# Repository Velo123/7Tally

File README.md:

# 7Tally

DRC config imported from: https://github.com/Cimos/KiCad-CustomDesignRules/tree/main#

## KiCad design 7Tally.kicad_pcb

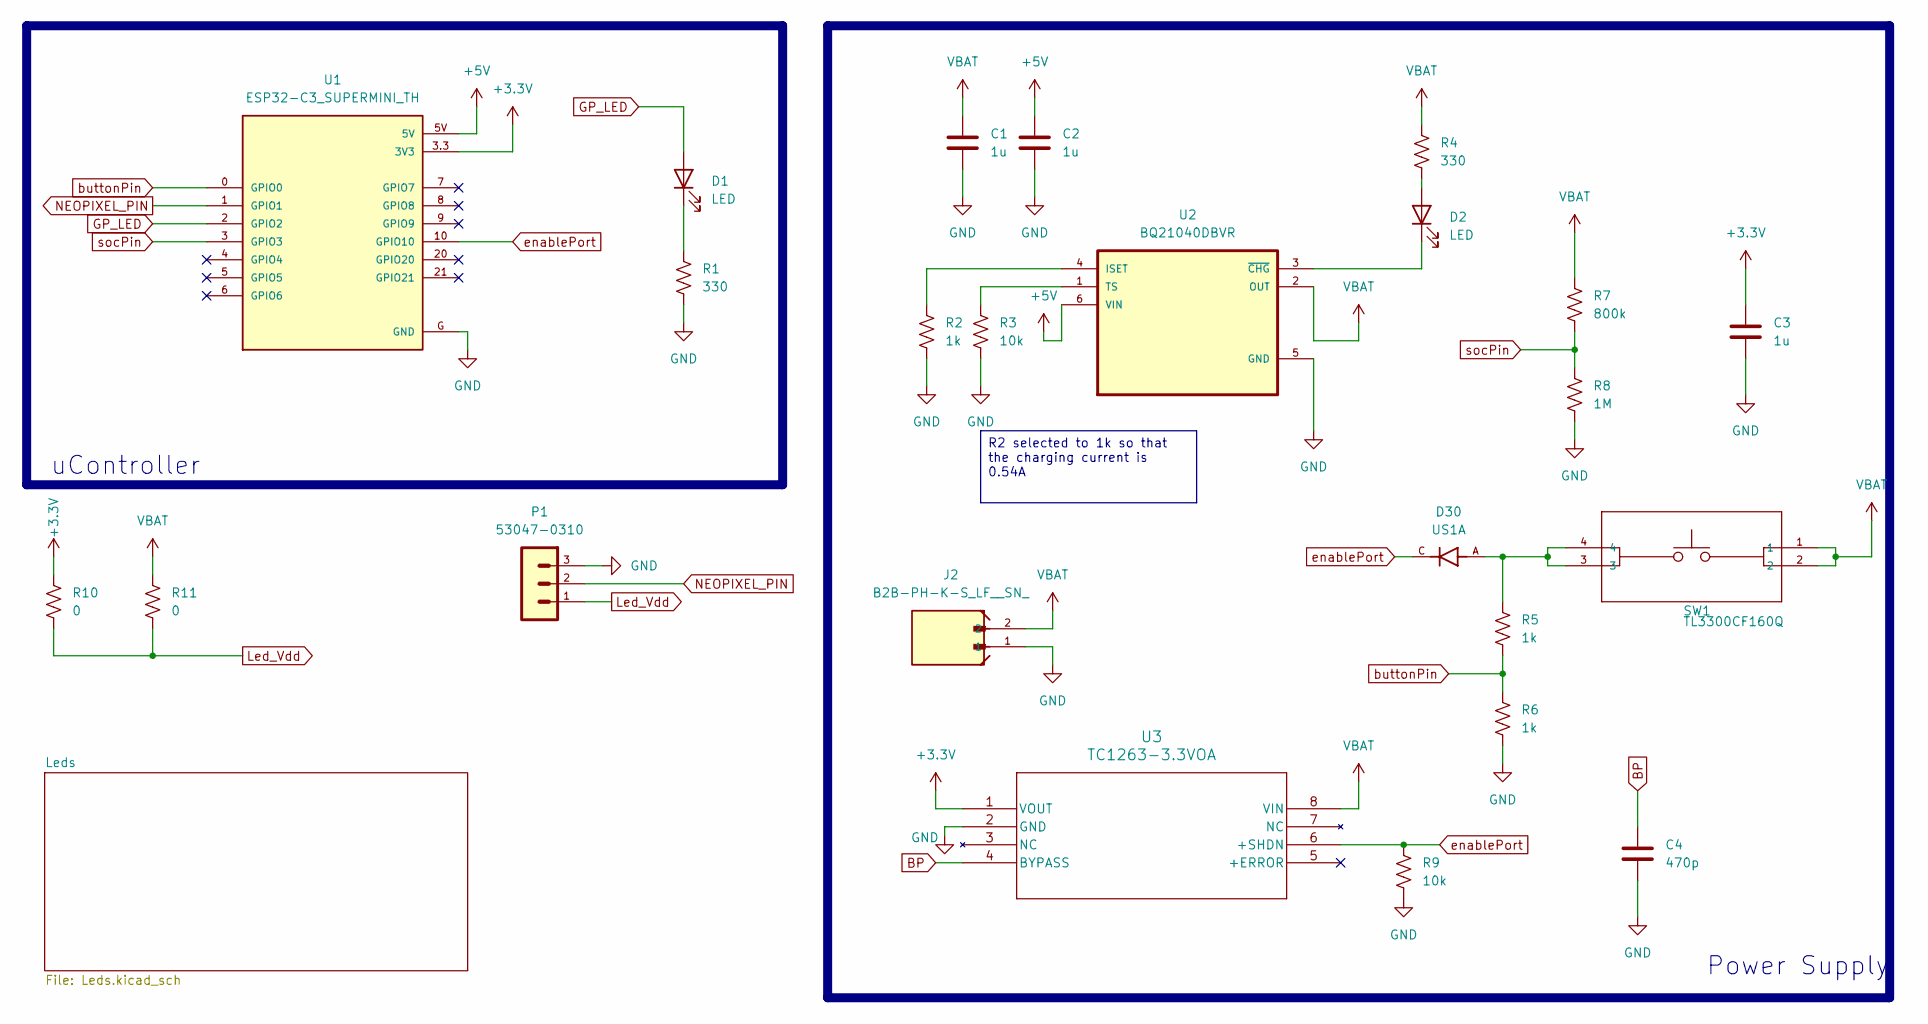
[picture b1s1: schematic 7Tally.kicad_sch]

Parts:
C1, C2, C3: 1u; C_0805_2012Metric
C4: 470p; C_0805_2012Metric
D1, D2: LED; LED_0805_2012Metric
D30: US1A; DIOM4325X250N; PARTREV L2102
J2: B2B-PH-K-S_LF__SN_; JST_B2B-PH-K-S_LF__SN_
P1: 53047-0310
R1, R4: 330; R_0805_2012Metric
R2, R5, R6: 1k; R_0805_2012Metric
R3, R9: 10k; R_0805_2012Metric
R7: 800k; R_0805_2012Metric
R8: 1M; R_0805_2012Metric
R10, R11: 0; R_0805_2012Metric
SW1: TL3300CF160Q; SW_TL3300CF160Q_EWI; MANUFACTURER_PART_NUMBER TL3300CF160Q
U1: ESP32-C3_SUPERMINI_TH; MODULE_ESP32-C3_SUPERMINI_TH
U2: BQ21040DBVR; SOT95P280X145-6N
U3: TC1263-3.3VOA; TC1263-3-3VOA_SOIC8-N_MC_MCH

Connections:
+3.3V: C3.1, R10.1, U1.3.3 (3V3), U3.1 (VOUT)
+5V: C2.1, U1.5V, U2.6 (VIN)
BP: C4.1, U3.4 (BYPASS)
GND: C1.2, C2.2, C3.2, C4.2, J2.1, P1.3, R1.2, R2.2, R3.2, R6.2, R8.2, R9.2, U1.G (GND), U2.5 (GND), U3.2 (GND); also elsewhere on the board
GP_LED: D1.2 (A), U1.2 (GPIO2)
Led_Vdd: P1.1, R10.2, R11.2; also elsewhere on the board
NEOPIXEL_PIN: P1.2, U1.1 (GPIO1); also elsewhere on the board
unnamed: D1.1 (K), R1.1
unnamed: D2.2 (A), R4.2
unnamed: D2.1 (K), U2.3 (~CHG)
unnamed: D30.A, R5.1, SW1.3, SW1.4
unnamed: R2.1, U2.4 (ISET)
unnamed: R3.1, U2.1 (TS)
VBAT: C1.1, J2.2, R4.1, R7.1, R11.1, SW1.1, SW1.2, U2.2 (OUT), U3.8 (VIN)
buttonPin: R5.2, R6.1, U1.0 (GPIO0)
enablePort: D30.C, R9.1, U1.10 (GPIO10), U3.6 (+SHDN)
socPin: R7.2, R8.1, U1.3 (GPIO3)

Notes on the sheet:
uController
Power Supply
R2 selected to 1k so that the charging current is 0.54A

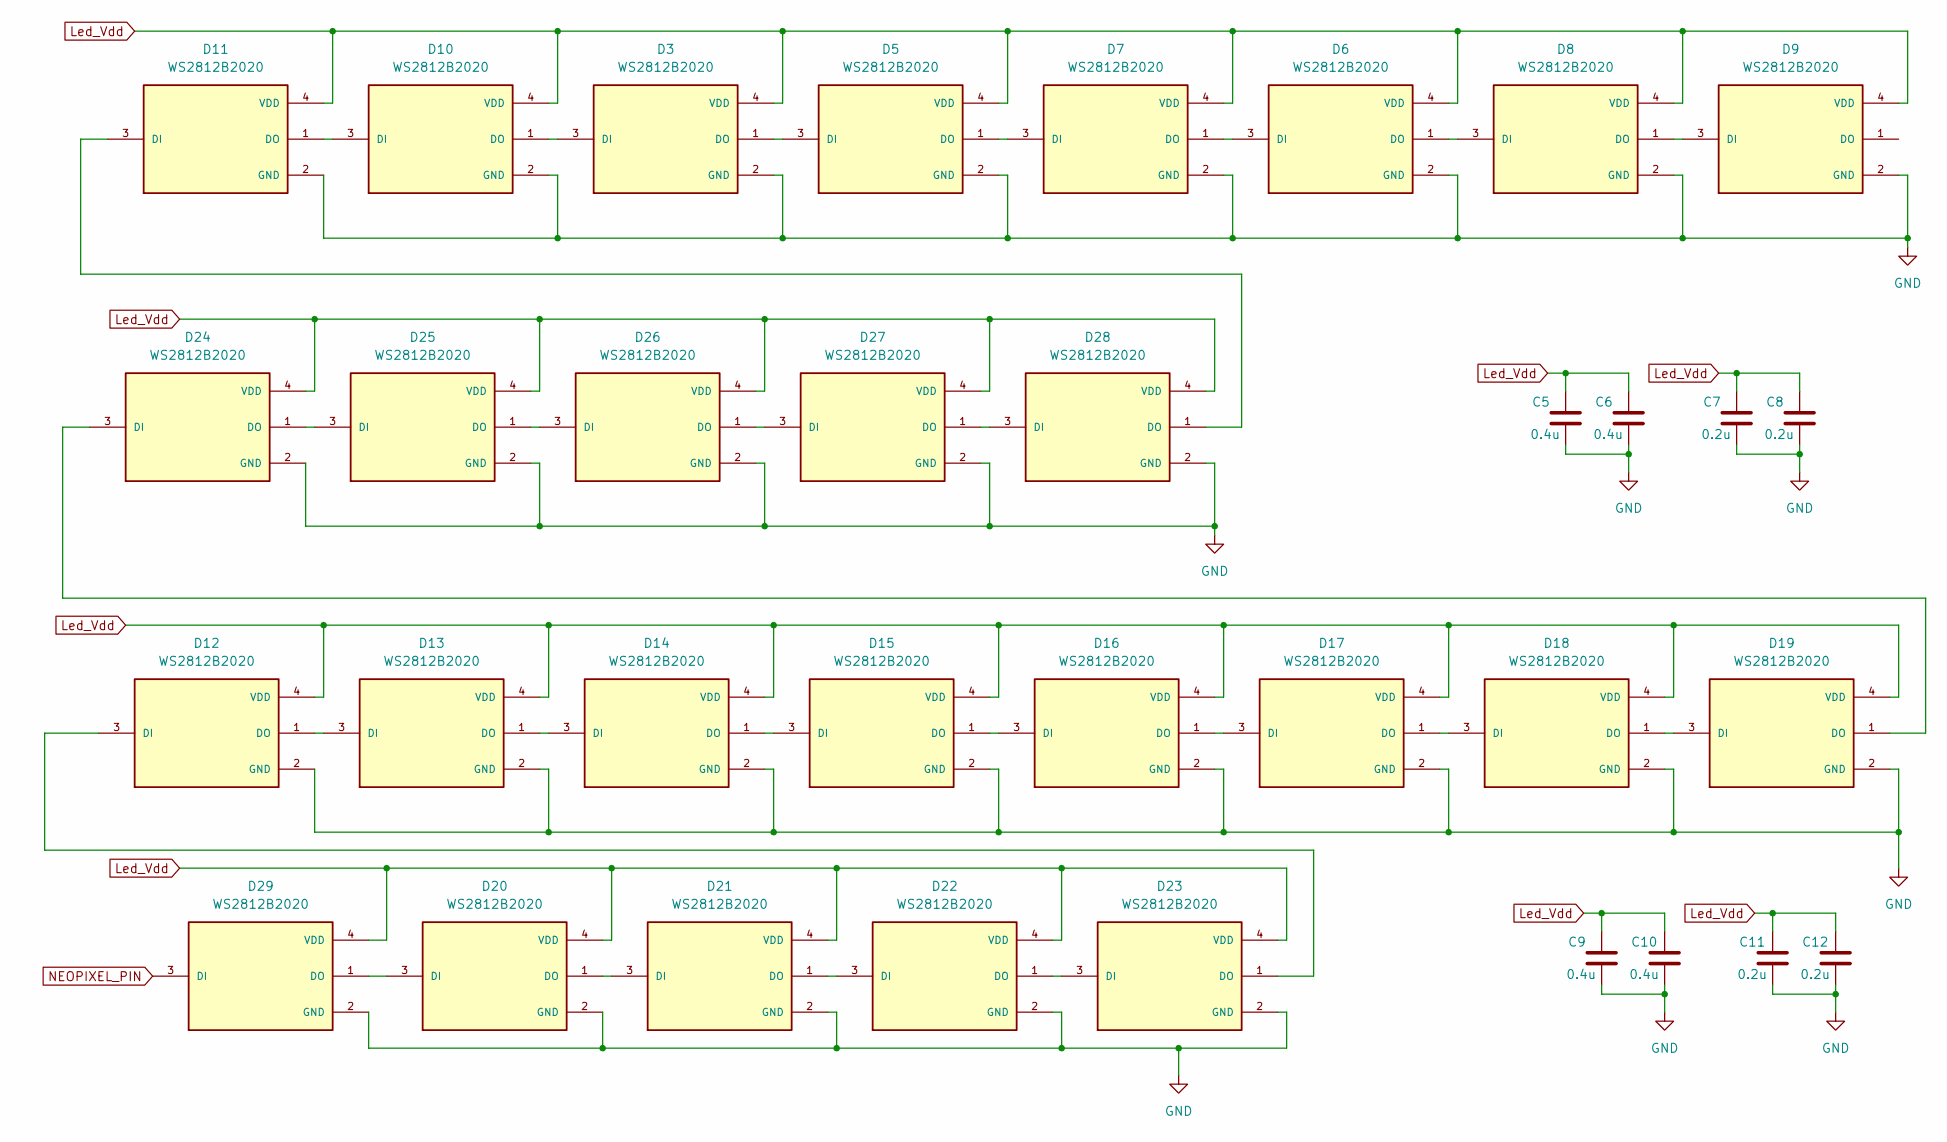
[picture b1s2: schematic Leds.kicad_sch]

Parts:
C5, C6, C9, C10: 0.4u; C_0201_0603Metric
C7, C8, C11, C12: 0.2u; C_0201_0603Metric
D3, D5, D6, D7, D8, D9, D10, D11, D12, D13, D14, D15, D16, D17, D18, D19, D20, D21, D22, D23, D24, D25, D26, D27, D28, D29: WS2812B2020; LED_WS2812B2020; PARTREV V1.0

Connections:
GND: C5.2, C6.2, C7.2, C8.2, C9.2, C10.2, C11.2, C12.2, D3.2 (GND), D5.2 (GND), D6.2 (GND), D7.2 (GND), D8.2 (GND), D9.2 (GND), D10.2 (GND), D11.2 (GND), D12.2 (GND), D13.2 (GND), D14.2 (GND), D15.2 (GND), D16.2 (GND), D17.2 (GND), D18.2 (GND), D19.2 (GND), D20.2 (GND), D21.2 (GND), D22.2 (GND), D23.2 (GND), D24.2 (GND), D25.2 (GND), D26.2 (GND), D27.2 (GND), D28.2 (GND), D29.2 (GND); also elsewhere on the board
Led_Vdd: C5.1, C6.1, C7.1, C8.1, C9.1, C10.1, C11.1, C12.1, D3.4 (VDD), D5.4 (VDD), D6.4 (VDD), D7.4 (VDD), D8.4 (VDD), D9.4 (VDD), D10.4 (VDD), D11.4 (VDD), D12.4 (VDD), D13.4 (VDD), D14.4 (VDD), D15.4 (VDD), D16.4 (VDD), D17.4 (VDD), D18.4 (VDD), D19.4 (VDD), D20.4 (VDD), D21.4 (VDD), D22.4 (VDD), D23.4 (VDD), D24.4 (VDD), D25.4 (VDD), D26.4 (VDD), D27.4 (VDD), D28.4 (VDD), D29.4 (VDD); also elsewhere on the board
NEOPIXEL_PIN: D29.3 (DI); also elsewhere on the board
unnamed: D3.1 (DO), D5.3 (DI)
unnamed: D5.1 (DO), D7.3 (DI)
unnamed: D6.3 (DI), D7.1 (DO)
unnamed: D6.1 (DO), D8.3 (DI)
unnamed: D8.1 (DO), D9.3 (DI)
unnamed: D10.3 (DI), D11.1 (DO)
unnamed: D3.3 (DI), D10.1 (DO)
unnamed: D11.3 (DI), D28.1 (DO)
unnamed: D12.3 (DI), D23.1 (DO)
unnamed: D12.1 (DO), D13.3 (DI)
unnamed: D13.1 (DO), D14.3 (DI)
unnamed: D14.1 (DO), D15.3 (DI)
unnamed: D15.1 (DO), D16.3 (DI)
unnamed: D16.1 (DO), D17.3 (DI)
unnamed: D17.1 (DO), D18.3 (DI)
unnamed: D18.1 (DO), D19.3 (DI)
unnamed: D19.1 (DO), D24.3 (DI)
unnamed: D20.3 (DI), D29.1 (DO)
unnamed: D20.1 (DO), D21.3 (DI)
unnamed: D21.1 (DO), D22.3 (DI)
unnamed: D22.1 (DO), D23.3 (DI)
unnamed: D24.1 (DO), D25.3 (DI)
unnamed: D25.1 (DO), D26.3 (DI)
unnamed: D26.1 (DO), D27.3 (DI)
unnamed: D27.1 (DO), D28.3 (DI)

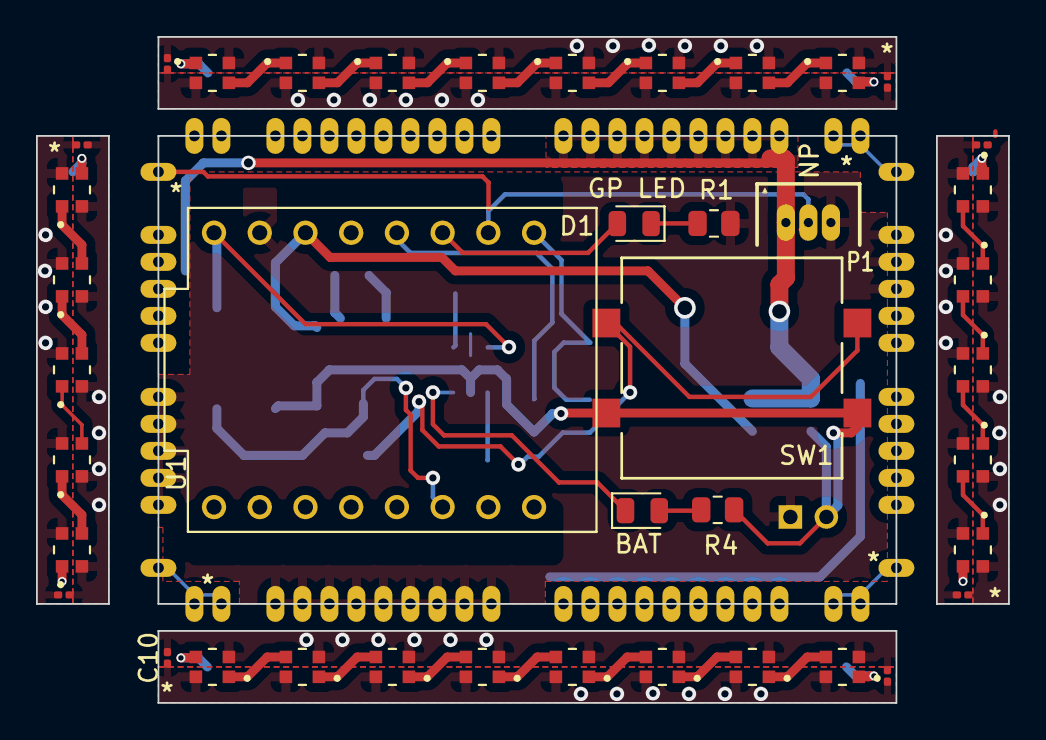
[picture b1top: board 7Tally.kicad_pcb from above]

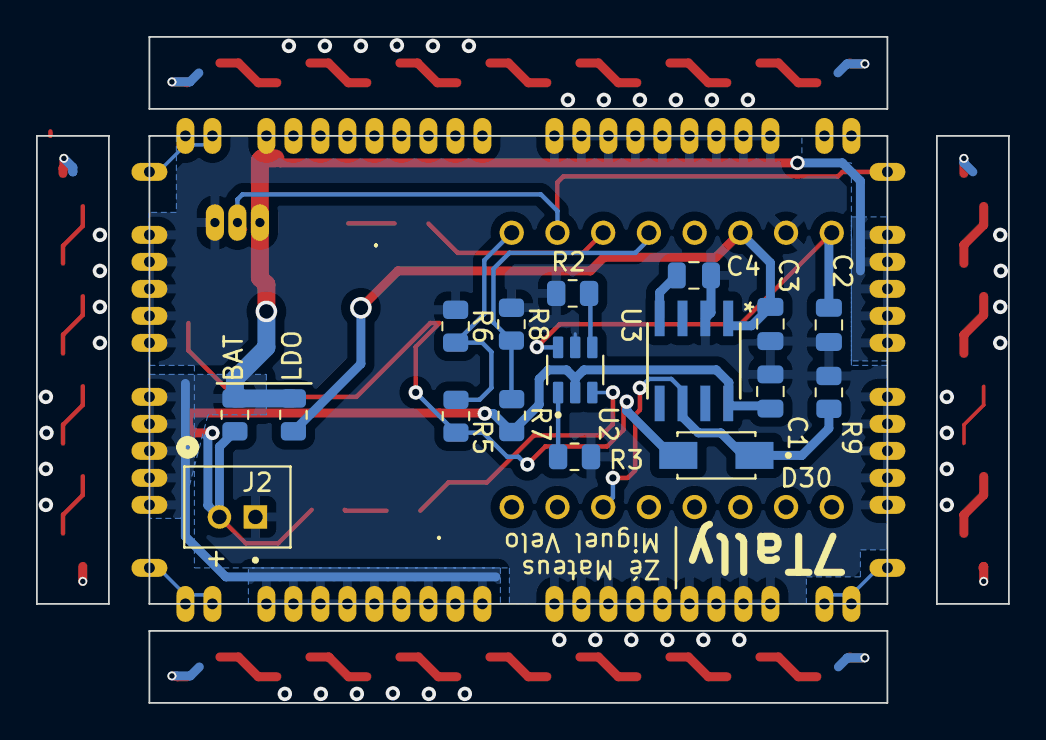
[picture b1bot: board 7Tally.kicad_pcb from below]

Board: 2 copper layers, 54.0 x 37.0 mm, 65 parts (17 on the bottom side), 42 nets.

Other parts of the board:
C-Edge-1mmx2mmx0.8mmTH, C-Edge-1mmx2mmx0.8mmTH#2, C-Edge-1mmx2mmx0.8mmTH#3, C-Edge-1mmx2mmx0.8mmTH#4, C-Edge-1mmx2mmx0.8mmTH#5, C-Edge-1mmx2mmx0.8mmTH#6, C-Edge-1mmx2mmx0.8mmTH#7: C-Edge-1mmx2mmx0.8mmTH

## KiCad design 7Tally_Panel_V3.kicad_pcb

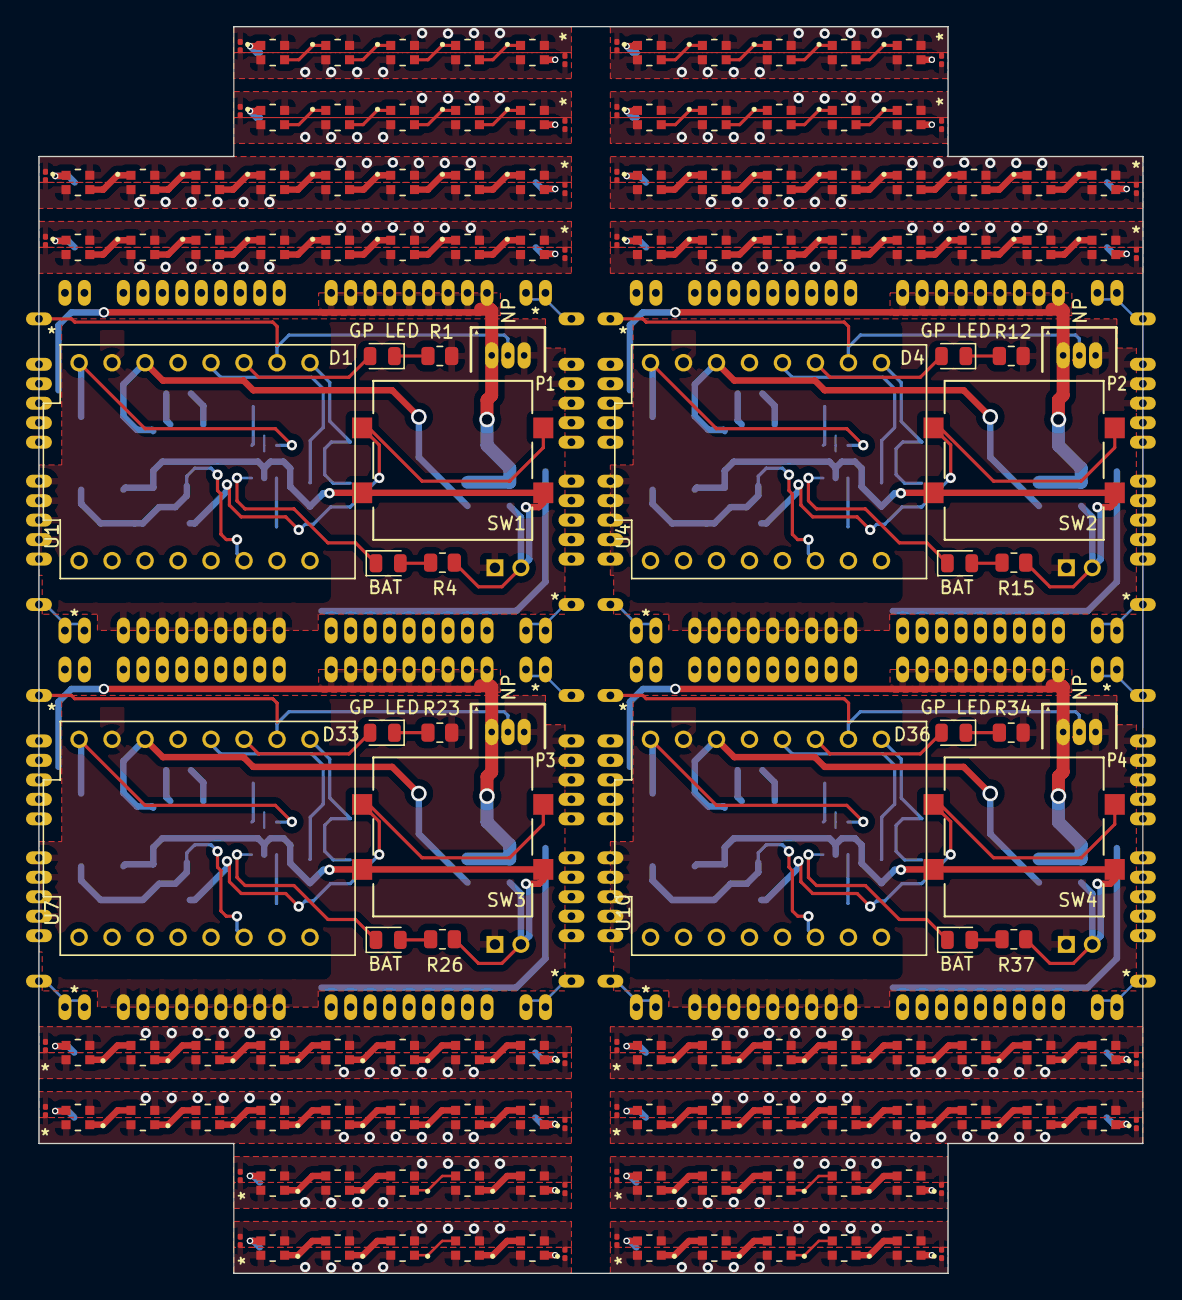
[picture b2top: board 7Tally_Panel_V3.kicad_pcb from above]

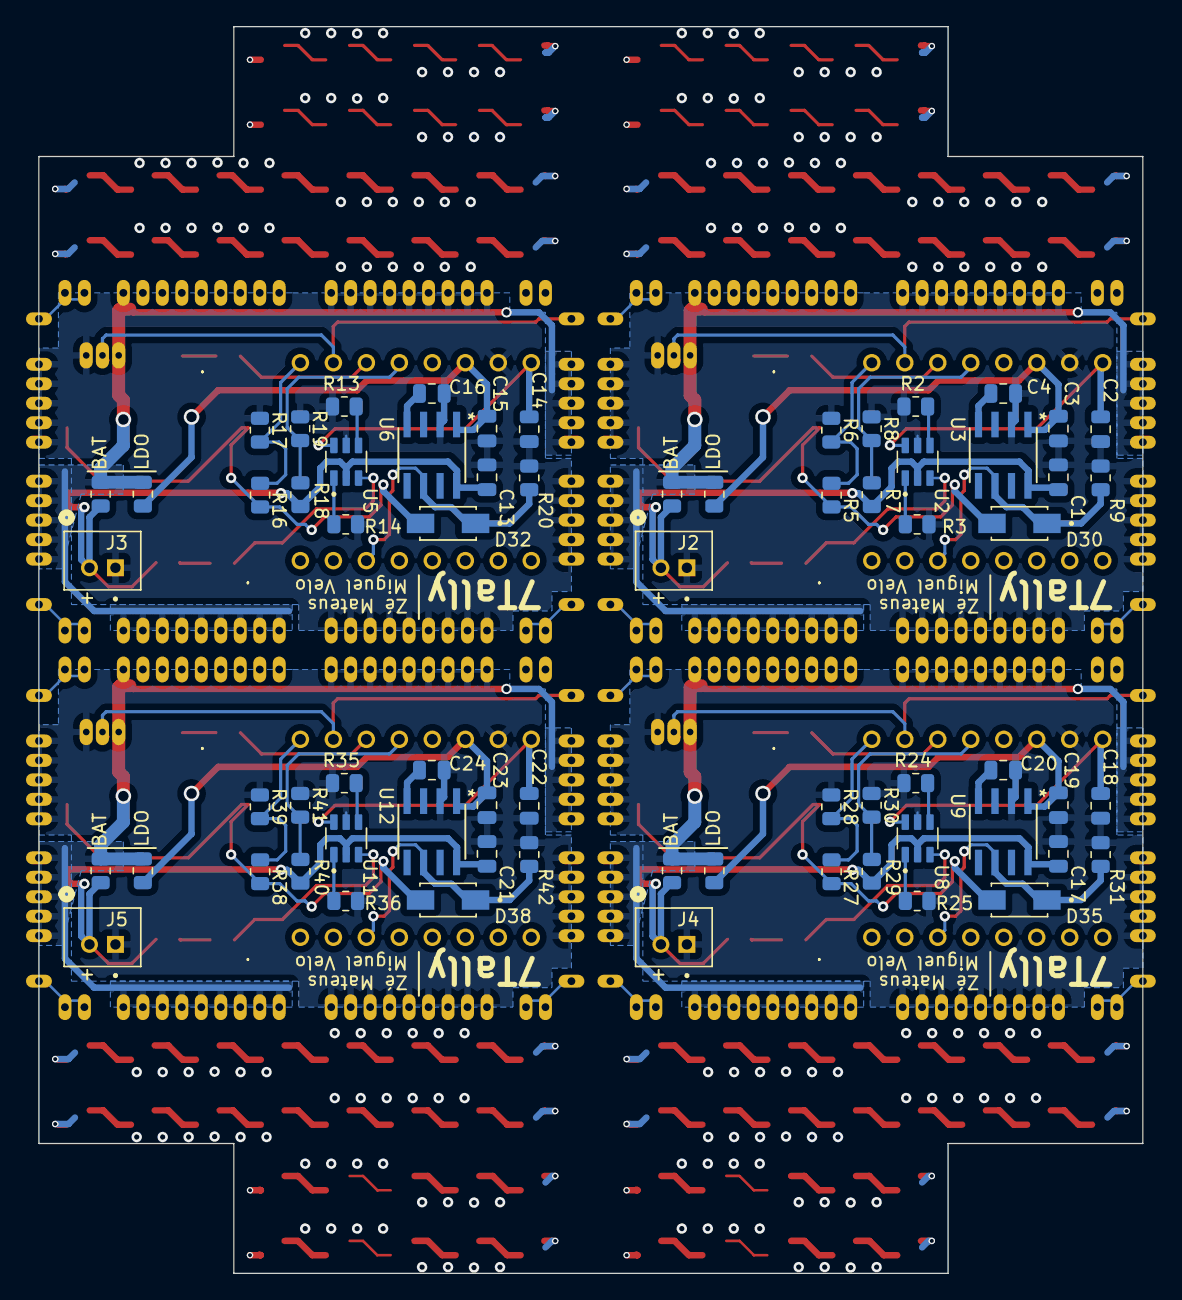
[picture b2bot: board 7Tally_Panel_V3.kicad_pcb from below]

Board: 2 copper layers, 85.0 x 96.0 mm, 443 parts (68 on the bottom side), 42 nets.

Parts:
1, 2, 3, 4, 5, 6, 7, 8, 9, 10, 11, 12, 13, 14, 15, 16, 17, 18, 19, 20, 21, 22, 23, 24, 25, 26, 27, 28, 29, 30, 31, 32, 33, 34, 35, 36, 37, 38, 39, 40, 41, 42, 43, 44, 45, 46, 47, 48, 49, 50, 51, 52, 53, 54, 55, 56, 57, 58, 59, 60, 61, 62, 63, 64, 65, 66, 67, 68, 69, 70, 71, 72, 73, 74, 75, 76, 77, 78, 79, 80, 81, 82, 83, 84, 85, 86, 87, 88, 89, 90, 91, 92, 93, 94, 95, 96, 97, 98, 99, 100, 101, 102, 103, 104, 105, 106, 107, 108, 109, 110, 111, 112, 113, 114, 115, 116, 117, 118, 119, 120, 121, 122, 123, 124, 125, 126, 127, 128, 129, 130, 131, 132, 133, 134, 135, 136, 137, 138, 139, 140, 141, 142, 143, 144, 145, 146, 147, 148, 149, 150, 151, 152, 153, 154, 155, 156, 157, 158, 159, 160, 161, 162, 163, 164, 165, 166, 167, 168, 169, 170, 171, 172, 173, 174, 175, 176, 177, 178, 179, 180, 181, 182, 183: (no value)
C1, C2, C3, C13, C14, C15, C17, C18, C19, C21, C22, C23: 1u; C_0805_2012Metric
C4, C16, C20, C24: 470p; C_0805_2012Metric
C5, C6, C9, C10, C25, C26, C27, C28, C29, C30, C31, C32, C33, C34, C35, C36: 0.4u; C_0201_0603Metric
C7, C8, C11, C12, C37, C38, C39, C40, C41, C42, C43, C44, C45, C46, C47, C48: 0.2u; C_0201_0603Metric
C-Edge-1mmx2mmx0.8mmTH, C-Edge-1mmx2mmx0.8mmTH1, C-Edge-1mmx2mmx0.8mmTH2, C-Edge-1mmx2mmx0.8mmTH3, C-Edge-1mmx2mmx0.8mmTH4, C-Edge-1mmx2mmx0.8mmTH5, C-Edge-1mmx2mmx0.8mmTH6, C-Edge-1mmx2mmx0.8mmTH7, C-Edge-1mmx2mmx0.8mmTH8, C-Edge-1mmx2mmx0.8mmTH9, C-Edge-1mmx2mmx0.8mmTH10, C-Edge-1mmx2mmx0.8mmTH11, C-Edge-1mmx2mmx0.8mmTH12, C-Edge-1mmx2mmx0.8mmTH13, C-Edge-1mmx2mmx0.8mmTH14, C-Edge-1mmx2mmx0.8mmTH15, C-Edge-1mmx2mmx0.8mmTH16, C-Edge-1mmx2mmx0.8mmTH17, C-Edge-1mmx2mmx0.8mmTH18, C-Edge-1mmx2mmx0.8mmTH19, C-Edge-1mmx2mmx0.8mmTH20, C-Edge-1mmx2mmx0.8mmTH21, C-Edge-1mmx2mmx0.8mmTH#2, C-Edge-1mmx2mmx0.8mmTH#3, C-Edge-1mmx2mmx0.8mmTH#4, C-Edge-1mmx2mmx0.8mmTH#5, C-Edge-1mmx2mmx0.8mmTH#6, C-Edge-1mmx2mmx0.8mmTH#7: C-Edge-1mmx2mmx0.8mmTH
D1, D2, D4, D31, D33, D34, D36, D37: LED; LED_0805_2012Metric
D3, D5, D6, D7, D8, D9, D10, D11, D12, D13, D14, D15, D16, D17, D18, D19, D20, D21, D22, D23, D24, D25, D26, D27, D28, D29, D39, D40, D41, D42, D43, D44, D45, D46, D47, D48, D49, D50, D51, D52, D53, D54, D55, D56, D57, D58, D59, D60, D61, D62, D63, D64, D65, D66, D67, D68, D69, D70, D71, D72, D73, D74, D75, D76, D77, D78, D79, D80, D81, D82, D83, D84, D85, D86, D87, D88, D89, D90, D91, D92, D93, D94, D95, D96, D97, D98, D99, D100, D101, D102, D103, D104, D105, D106, D107, D108, D109, D110, D111, D112, D113, D114, D115, D116: WS2812B2020; LED_WS2812B2020
D30, D32, D35, D38: US1A; DIOM4325X250N
J2, J3, J4, J5: B2B-PH-K-S_LF__SN_; JST_B2B-PH-K-S_LF__SN_
P1, P2, P3, P4: 53047-0310
R1, R4, R12, R15, R23, R26, R34, R37: 330; R_0805_2012Metric
R2, R5, R6, R13, R16, R17, R24, R27, R28, R35, R38, R39: 1k; R_0805_2012Metric
R3, R9, R14, R20, R25, R31, R36, R42: 10k; R_0805_2012Metric
R7, R18, R29, R40: 800k; R_0805_2012Metric
R8, R19, R30, R41: 1M; R_0805_2012Metric
R10, R11, R21, R22, R32, R33, R43, R44: 0; R_0805_2012Metric
SW1, SW2, SW3, SW4: TL3300CF160Q; SW_TL3300CF160Q_EWI
U1, U4, U7, U10: ESP32-C3_SUPERMINI_TH; MODULE_ESP32-C3_SUPERMINI_TH
U2, U5, U8, U11: BQ21040DBVR; SOT95P280X145-6N
U3, U6, U9, U12: TC1263-3.3VOA; TC1263-3-3VOA_SOIC8-N_MC_MCH

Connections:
+3.3V: C3.1, C15.1, C19.1, C23.1, R10.1, R21.1, R32.1, R43.1, U1.3.3 (3V3), U3.1 (VOUT), U4.3.3 (3V3), U6.1 (VOUT), U7.3.3 (3V3), U9.1 (VOUT), U10.3.3 (3V3), U12.1 (VOUT)
+5V: C2.1, C14.1, C18.1, C22.1, U1.5V, U2.6 (VIN), U4.5V, U5.6 (VIN), U7.5V, U8.6 (VIN), U10.5V, U11.6 (VIN)
BP: C4.1, C16.1, C20.1, C24.1, U3.4 (BYPASS), U6.4 (BYPASS), U9.4 (BYPASS), U12.4 (BYPASS)
GND: C1.2, C2.2, C3.2, C4.2, C5.2, C6.2, C7.2, C8.2, C9.2, C10.2, C11.2, C12.2, C13.2, C14.2, C15.2, C16.2, C17.2, C18.2, C19.2, C20.2, C21.2, C22.2, C23.2, C24.2, C25.2, C26.2, C27.2, C28.2, C29.2, C30.2, C31.2, C32.2, C33.2, C34.2, C35.2, C36.2, C37.2, C38.2, C39.2, C40.2, C41.2, C42.2, C43.2, C44.2, C45.2, C46.2, C47.2, C48.2, D3.2 (GND), D5.2 (GND), D6.2 (GND), D7.2 (GND), D8.2 (GND), D9.2 (GND), D10.2 (GND), D11.2 (GND), D12.2 (GND), D13.2 (GND), D14.2 (GND), D15.2 (GND), D16.2 (GND), D17.2 (GND), D18.2 (GND), D19.2 (GND), D20.2 (GND), D21.2 (GND), D22.2 (GND), D23.2 (GND), D24.2 (GND), D25.2 (GND), D26.2 (GND), D27.2 (GND), D28.2 (GND), D29.2 (GND), D39.2 (GND), D40.2 (GND), D41.2 (GND), D42.2 (GND), D43.2 (GND), D44.2 (GND), D45.2 (GND), D46.2 (GND), D47.2 (GND), D48.2 (GND), D49.2 (GND), D50.2 (GND), D51.2 (GND), D52.2 (GND), D53.2 (GND), D54.2 (GND), D55.2 (GND), D56.2 (GND), D57.2 (GND), D58.2 (GND), D59.2 (GND), D60.2 (GND), D61.2 (GND), D62.2 (GND), D63.2 (GND), D64.2 (GND), D65.2 (GND), D66.2 (GND), D67.2 (GND), D68.2 (GND), D69.2 (GND), D70.2 (GND), D71.2 (GND), D72.2 (GND), D73.2 (GND), D74.2 (GND), D75.2 (GND), D76.2 (GND), D77.2 (GND), D78.2 (GND), D79.2 (GND), D80.2 (GND), D81.2 (GND), D82.2 (GND), D83.2 (GND), D84.2 (GND), D85.2 (GND), D86.2 (GND), D87.2 (GND), D88.2 (GND), D89.2 (GND), D90.2 (GND), D91.2 (GND), D92.2 (GND), D93.2 (GND), D94.2 (GND), D95.2 (GND), D96.2 (GND), D97.2 (GND), D98.2 (GND), D99.2 (GND), D100.2 (GND), D101.2 (GND), D102.2 (GND), D103.2 (GND), D104.2 (GND), D105.2 (GND), D106.2 (GND), D107.2 (GND), D108.2 (GND), D109.2 (GND), D110.2 (GND), D111.2 (GND), D112.2 (GND), D113.2 (GND), D114.2 (GND), D115.2 (GND), D116.2 (GND), J2.1, J3.1, J4.1, J5.1, P1.3, P2.3, P3.3, P4.3, R1.2, R2.2, R3.2, R6.2, R8.2, R9.2, R12.2, R13.2, R14.2, R17.2, R19.2, R20.2, R23.2, R24.2, R25.2, R28.2, R30.2, R31.2, R34.2, R35.2, R36.2, R39.2, R41.2, R42.2, U1.G (GND), U2.5 (GND), U3.2 (GND), U4.G (GND), U5.5 (GND), U6.2 (GND), U7.G (GND), U8.5 (GND), U9.2 (GND), U10.G (GND), U11.5 (GND), U12.2 (GND)
GP_LED: D1.2 (A), D4.2 (A), D33.2 (A), D36.2 (A), U1.2 (GPIO2), U4.2 (GPIO2), U7.2 (GPIO2), U10.2 (GPIO2)
Led_Vdd: C5.1, C6.1, C7.1, C8.1, C9.1, C10.1, C11.1, C12.1, C25.1, C26.1, C27.1, C28.1, C29.1, C30.1, C31.1, C32.1, C33.1, C34.1, C35.1, C36.1, C37.1, C38.1, C39.1, C40.1, C41.1, C42.1, C43.1, C44.1, C45.1, C46.1, C47.1, C48.1, D3.4 (VDD), D5.4 (VDD), D6.4 (VDD), D7.4 (VDD), D8.4 (VDD), D9.4 (VDD), D10.4 (VDD), D11.4 (VDD), D12.4 (VDD), D13.4 (VDD), D14.4 (VDD), D15.4 (VDD), D16.4 (VDD), D17.4 (VDD), D18.4 (VDD), D19.4 (VDD), D20.4 (VDD), D21.4 (VDD), D22.4 (VDD), D23.4 (VDD), D24.4 (VDD), D25.4 (VDD), D26.4 (VDD), D27.4 (VDD), D28.4 (VDD), D29.4 (VDD), D39.4 (VDD), D40.4 (VDD), D41.4 (VDD), D42.4 (VDD), D43.4 (VDD), D44.4 (VDD), D45.4 (VDD), D46.4 (VDD), D47.4 (VDD), D48.4 (VDD), D49.4 (VDD), D50.4 (VDD), D51.4 (VDD), D52.4 (VDD), D53.4 (VDD), D54.4 (VDD), D55.4 (VDD), D56.4 (VDD), D57.4 (VDD), D58.4 (VDD), D59.4 (VDD), D60.4 (VDD), D61.4 (VDD), D62.4 (VDD), D63.4 (VDD), D64.4 (VDD), D65.4 (VDD), D66.4 (VDD), D67.4 (VDD), D68.4 (VDD), D69.4 (VDD), D70.4 (VDD), D71.4 (VDD), D72.4 (VDD), D73.4 (VDD), D74.4 (VDD), D75.4 (VDD), D76.4 (VDD), D77.4 (VDD), D78.4 (VDD), D79.4 (VDD), D80.4 (VDD), D81.4 (VDD), D82.4 (VDD), D83.4 (VDD), D84.4 (VDD), D85.4 (VDD), D86.4 (VDD), D87.4 (VDD), D88.4 (VDD), D89.4 (VDD), D90.4 (VDD), D91.4 (VDD), D92.4 (VDD), D93.4 (VDD), D94.4 (VDD), D95.4 (VDD), D96.4 (VDD), D97.4 (VDD), D98.4 (VDD), D99.4 (VDD), D100.4 (VDD), D101.4 (VDD), D102.4 (VDD), D103.4 (VDD), D104.4 (VDD), D105.4 (VDD), D106.4 (VDD), D107.4 (VDD), D108.4 (VDD), D109.4 (VDD), D110.4 (VDD), D111.4 (VDD), D112.4 (VDD), D113.4 (VDD), D114.4 (VDD), D115.4 (VDD), D116.4 (VDD), P1.1, P2.1, P3.1, P4.1, R10.2, R11.2, R21.2, R22.2, R32.2, R33.2, R43.2, R44.2
NEOPIXEL_PIN: D29.3 (DI), D91.3 (DI), D96.3 (DI), D101.3 (DI), P1.2, P2.2, P3.2, P4.2, U1.1 (GPIO1), U4.1 (GPIO1), U7.1 (GPIO1), U10.1 (GPIO1)
unnamed: D1.1 (K), D4.1 (K), D33.1 (K), D36.1 (K), R1.1, R12.1, R23.1, R34.1
unnamed: D2.2 (A), D31.2 (A), D34.2 (A), D37.2 (A), R4.2, R15.2, R26.2, R37.2
unnamed: D2.1 (K), D31.1 (K), D34.1 (K), D37.1 (K), U2.3 (~CHG), U5.3 (~CHG), U8.3 (~CHG), U11.3 (~CHG)
unnamed: D3.1 (DO), D5.3 (DI), D39.1 (DO), D40.3 (DI), D47.1 (DO), D48.3 (DI), D55.1 (DO), D56.3 (DI)
unnamed: D5.1 (DO), D7.3 (DI), D40.1 (DO), D42.3 (DI), D48.1 (DO), D50.3 (DI), D56.1 (DO), D58.3 (DI)
unnamed: D6.3 (DI), D7.1 (DO), D41.3 (DI), D42.1 (DO), D49.3 (DI), D50.1 (DO), D57.3 (DI), D58.1 (DO)
unnamed: D6.1 (DO), D8.3 (DI), D41.1 (DO), D43.3 (DI), D49.1 (DO), D51.3 (DI), D57.1 (DO), D59.3 (DI)
unnamed: D8.1 (DO), D9.3 (DI), D43.1 (DO), D44.3 (DI), D51.1 (DO), D52.3 (DI), D59.1 (DO), D60.3 (DI)
unnamed: D10.3 (DI), D11.1 (DO), D45.3 (DI), D46.1 (DO), D53.3 (DI), D54.1 (DO), D61.3 (DI), D62.1 (DO)
unnamed: D3.3 (DI), D10.1 (DO), D39.3 (DI), D45.1 (DO), D47.3 (DI), D53.1 (DO), D55.3 (DI), D61.1 (DO)
unnamed: D11.3 (DI), D28.1 (DO), D46.3 (DI), D54.3 (DI), D62.3 (DI), D106.1 (DO), D111.1 (DO), D116.1 (DO)
unnamed: D12.3 (DI), D23.1 (DO), D63.3 (DI), D71.3 (DI), D79.3 (DI), D90.1 (DO), D95.1 (DO), D100.1 (DO)
unnamed: D12.1 (DO), D13.3 (DI), D63.1 (DO), D64.3 (DI), D71.1 (DO), D72.3 (DI), D79.1 (DO), D80.3 (DI)
unnamed: D13.1 (DO), D14.3 (DI), D64.1 (DO), D65.3 (DI), D72.1 (DO), D73.3 (DI), D80.1 (DO), D81.3 (DI)
unnamed: D14.1 (DO), D15.3 (DI), D65.1 (DO), D66.3 (DI), D73.1 (DO), D74.3 (DI), D81.1 (DO), D82.3 (DI)
unnamed: D15.1 (DO), D16.3 (DI), D66.1 (DO), D67.3 (DI), D74.1 (DO), D75.3 (DI), D82.1 (DO), D83.3 (DI)
unnamed: D16.1 (DO), D17.3 (DI), D67.1 (DO), D68.3 (DI), D75.1 (DO), D76.3 (DI), D83.1 (DO), D84.3 (DI)
unnamed: D17.1 (DO), D18.3 (DI), D68.1 (DO), D69.3 (DI), D76.1 (DO), D77.3 (DI), D84.1 (DO), D85.3 (DI)
unnamed: D18.1 (DO), D19.3 (DI), D69.1 (DO), D70.3 (DI), D77.1 (DO), D78.3 (DI), D85.1 (DO), D86.3 (DI)
unnamed: D19.1 (DO), D24.3 (DI), D70.1 (DO), D78.1 (DO), D86.1 (DO), D102.3 (DI), D107.3 (DI), D112.3 (DI)
unnamed: D20.3 (DI), D29.1 (DO), D87.3 (DI), D91.1 (DO), D92.3 (DI), D96.1 (DO), D97.3 (DI), D101.1 (DO)
unnamed: D20.1 (DO), D21.3 (DI), D87.1 (DO), D88.3 (DI), D92.1 (DO), D93.3 (DI), D97.1 (DO), D98.3 (DI)
unnamed: D21.1 (DO), D22.3 (DI), D88.1 (DO), D89.3 (DI), D93.1 (DO), D94.3 (DI), D98.1 (DO), D99.3 (DI)
unnamed: D22.1 (DO), D23.3 (DI), D89.1 (DO), D90.3 (DI), D94.1 (DO), D95.3 (DI), D99.1 (DO), D100.3 (DI)
unnamed: D24.1 (DO), D25.3 (DI), D102.1 (DO), D103.3 (DI), D107.1 (DO), D108.3 (DI), D112.1 (DO), D113.3 (DI)
unnamed: D25.1 (DO), D26.3 (DI), D103.1 (DO), D104.3 (DI), D108.1 (DO), D109.3 (DI), D113.1 (DO), D114.3 (DI)
unnamed: D26.1 (DO), D27.3 (DI), D104.1 (DO), D105.3 (DI), D109.1 (DO), D110.3 (DI), D114.1 (DO), D115.3 (DI)
unnamed: D27.1 (DO), D28.3 (DI), D105.1 (DO), D106.3 (DI), D110.1 (DO), D111.3 (DI), D115.1 (DO), D116.3 (DI)
unnamed: D30.A, D32.A, D35.A, D38.A, R5.1, R16.1, R27.1, R38.1, SW1.3, SW1.4, SW2.3, SW2.4, SW3.3, SW3.4, SW4.3, SW4.4
unnamed: R2.1, R13.1, R24.1, R35.1, U2.4 (ISET), U5.4 (ISET), U8.4 (ISET), U11.4 (ISET)
unnamed: R3.1, R14.1, R25.1, R36.1, U2.1 (TS), U5.1 (TS), U8.1 (TS), U11.1 (TS)
VBAT: C1.1, C13.1, C17.1, C21.1, J2.2, J3.2, J4.2, J5.2, R4.1, R7.1, R11.1, R15.1, R18.1, R22.1, R26.1, R29.1, R33.1, R37.1, R40.1, R44.1, SW1.1, SW1.2, SW2.1, SW2.2, SW3.1, SW3.2, SW4.1, SW4.2, U2.2 (OUT), U3.8 (VIN), U5.2 (OUT), U6.8 (VIN), U8.2 (OUT), U9.8 (VIN), U11.2 (OUT), U12.8 (VIN)
buttonPin: R5.2, R6.1, R16.2, R17.1, R27.2, R28.1, R38.2, R39.1, U1.0 (GPIO0), U4.0 (GPIO0), U7.0 (GPIO0), U10.0 (GPIO0)
enablePort: D30.C, D32.C, D35.C, D38.C, R9.1, R20.1, R31.1, R42.1, U1.10 (GPIO10), U3.6 (+SHDN), U4.10 (GPIO10), U6.6 (+SHDN), U7.10 (GPIO10), U9.6 (+SHDN), U10.10 (GPIO10), U12.6 (+SHDN)
socPin: R7.2, R8.1, R18.2, R19.1, R29.2, R30.1, R40.2, R41.1, U1.3 (GPIO3), U4.3 (GPIO3), U7.3 (GPIO3), U10.3 (GPIO3)

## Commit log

2025-09-09 schematic: missing connectors
2025-09-09 schematic: added connectors
2025-09-10 schematic:error fix
2025-09-18 feat(DRC): Imported DRC rules from JLCPCB
2025-09-18 chore(PCB): added 3D models and start PCB
2025-09-18 feat(PCB): start of routing
2025-09-18 feat(PCB): finished routing
2025-09-18 feat(PCB): finished V1
    First version fully connected - DRC missing
2025-09-19 chore(PCB): Passed DRC
2025-09-26 feat(PCB): Start leds
2025-09-28 feat(PCB): start of castellated edges implementation
2025-09-30 feat(PCB): finalized initial PCB
2025-10-04 feat(PCB): Panelization
2025-10-04 chore(PCB): removed mousebites submodule
2025-10-13 feat(PCB): Added panelization
2025-10-16 chore(PCB): final touches
2025-10-16 chore(PCB): fix readme MD
2025-10-17 fix(PCB): Small problem fixing
2025-10-18 fix(PCB): pos-israel meet
2025-10-19 chore(PCB): Final Version
2025-10-26 feat(PCB): New PCB panel

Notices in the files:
parts and their libraries:
COPYRIGHT: Copyright (C) 2025 Ultra Librarian. All rights reserved.
